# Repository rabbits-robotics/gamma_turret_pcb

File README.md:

# gamma_turret_pcb

## 役割

砲塔側の制御基板。M5Stack Stamp-P4（ESP32-P4）を載せ、CAN 2 系統、射出 ESC の PWM 2ch、装填サーボの半二重 UART、上位コントローラとの UART、IMU を 1 枚にまとめる。

## 主要部品

| 部品 | 型番 | 用途 |
|---|---|---|
| マイコンモジュール | M5Stack Stamp-P4（ESP32-P4） | 制御。ピンソケットで差し替え可 |
| CAN トランシーバ | MCP2562-E/P × 2 | CAN1（砲塔・ジンバル系）、CAN2（車体系） |
| レギュレータ | M78AR05-1 | 24V → 5V（Stamp-P4 用） |
| IMU | BNO055 | 姿勢。UART 接続 |
| 24V コネクタ | AMASS XT30PW-M × 2、XT30PW-F × 1 | 24V 入力、外部 DCDC への往復 |
| CAN / ESC 信号 | JST PH S2B-PH-K × 4 | CAN1、CAN2、射出 ESC 左右 |
| ESC 電源 | JST XH S2B-XH-A × 2 | 射出 ESC 左右 |
| サーボ / 上位 UART | JST XH S3B-XH-A × 2 | ST3215（半二重）、上位コントローラ |
| CAN 終端抵抗 | 120 Ω × 2 | CAN1 / CAN2 |
| 表示・操作 | LED × 6、タクト SW × 2 | 電源 / デバッグ / アクティビティ、BOOT / RESET |

回路図は [gamma_turret.pdf](./gamma_turret.pdf)、部品表は [bom.csv](./bom.csv)、3D は [gamma_turret.step](./gamma_turret.step)。
設計時の検討は [docs/](./docs/) に、旧 STM32 版の設計は [old_design/](./old_design/) に残している。

## v1.0 の注意

- 未配線 1 箇所をジャンパで対応している（D1 のアノード側。[docs/2026-10-18-v1.0-power-on.md](./docs/2026-10-18-v1.0-power-on.md)）
- Stamp-P4 の USB-C から基板の 5V 系へ電流が流れる。USB だけで 5V 系（CAN トランシーバ、LED、UART）は動く。24V と USB を同時につないでも実用上は問題ないが、設計意図ではないため改版で逆流防止を入れる予定

## ライセンス

© Rabbits Robotics、[CERN-OHL-P-2.0](./LICENSE)。

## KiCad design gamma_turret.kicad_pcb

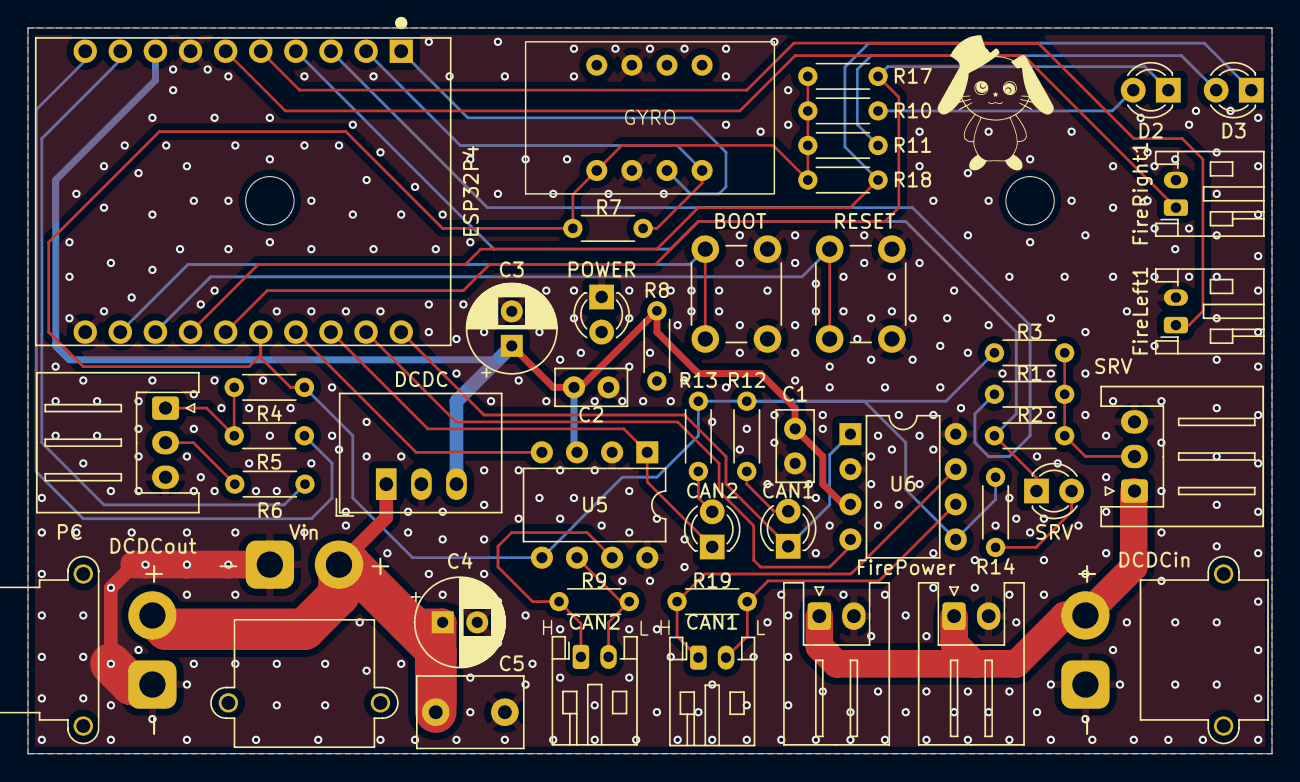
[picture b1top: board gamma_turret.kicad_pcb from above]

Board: 2 copper layers, 90.0 x 52.5 mm, 46 parts (0 on the bottom side), 34 nets.

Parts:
BOOT: SW_Push; SW_PUSH_6mm
C1, C2: 100n; C_Disc_D5.0mm_W2.5mm_P2.50mm
C3, C4: 100u; CP_Radial_D6.3mm_P2.50mm
C5: 22u; C_Disc_D7.5mm_W5.0mm_P5.00mm
CAN1, CAN2#2: LED; LED_D3.0mm
CAN1#2, CAN2: Conn_01x02; JST_PH_S2B-PH-K_1x02_P2.00mm_Horizontal
D2, D3: LED; LED_D3.0mm
DCDC: M78AR05-1; Converter_DCDC_RECOM_R-78E-0.5_THT
DCDCin: Conn_01x02; AMASS_XT30PW-M_1x02_P2.50mm_Horizontal
DCDCout: Conn_01x02; AMASS_XT30PW-F_1x02_P2.50mm_Horizontal
ESP32P4: M5Stack_Stamp-P4; Stamp-P4_Socket_2x10_P2.54mm_RS20.32mm
FireLeft1: Conn_01x02; JST_PH_S2B-PH-K_1x02_P2.00mm_Horizontal
FirePower, FirePower2: Conn_01x02; JST_XH_S2B-XH-A_1x02_P2.50mm_Horizontal
FireRight1: Conn_01x02; JST_PH_S2B-PH-K_1x02_P2.00mm_Horizontal
GYRO: BNO055
PC: Conn_01x03; JST_XH_S3B-XH-A_1x03_P2.50mm_Horizontal
POWER: LED; LED_D3.0mm
R1, R2, R8, R10, R11, R12, R13, R14: 1k; R_Axial_DIN0204_L3.6mm_D1.6mm_P5.08mm_Horizontal
R3, R4, R7, R17, R18: 10k; R_Axial_DIN0204_L3.6mm_D1.6mm_P5.08mm_Horizontal
R5, R6: 220; R_Axial_DIN0204_L3.6mm_D1.6mm_P5.08mm_Horizontal
R9, R19: 120; R_Axial_DIN0204_L3.6mm_D1.6mm_P5.08mm_Horizontal
RESET: SW_Push; SW_PUSH_6mm
SRV: LED; LED_D3.0mm
SRV#2: Conn_01x03; JST_XH_S3B-XH-A_1x03_P2.50mm_Horizontal
U5, U6: MCP2562-E-P; DIP-8_W7.62mm
Vin: Conn_01x02; AMASS_XT30PW-M_1x02_P2.50mm_Horizontal

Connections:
+3V3: ESP32P4.15 (3V3_OUT), GYRO.1 (VIN), R3.1, R4.1, R7.1, R10.1, R11.1, R12.1, R13.1, R14.1, R17.1, R18.1, U5.5 (Vio), U6.5 (Vio)
+5V: C1.1, C2.1, C3.1, DCDC.3 (VOUT), ESP32P4.8 (VBUS_5V), R8.1, U5.3 (VDD), U6.3 (VDD)
+7.5V: DCDCin.2, FirePower.1, FirePower2.1, SRV#2.1
+24V: C4.1, C5.1, DCDC.1 (VIN), DCDCout.2, Vin.2
/CAN1_RX: ESP32P4.12 (G21), U6.4 (RXD)
/CAN1_TX: CAN1.1 (K), ESP32P4.11 (G23), U6.1 (TXD)
/CAN2_RX: ESP32P4.14 (G17), U5.4 (RXD)
/CAN2_TX: CAN2#2.1 (K), ESP32P4.13 (G19), U5.1 (TXD)
/FIRE_LEFT_MOTOR: ESP32P4.5 (G1), FireLeft1.1
/FIRE_RIGHT_MOTOR: ESP32P4.6 (G0), FireRight1.1
/IMU_RX: ESP32P4.1 (G15), GYRO.3 (SDA/T)
/IMU_TX: ESP32P4.2 (G12), GYRO.4 (SCL/R), R7.2
/PC_RX: ESP32P4.9 (G27), R6.1
/PC_TX: ESP32P4.10 (G26), R5.1
/SRV_RX: ESP32P4.3 (G10), R1.1
/SRV_TX: ESP32P4.4 (G8), R2.2, SRV.1 (K)
GND: BOOT.2, C1.2, C2.2, C3.2, C4.2, C5.2, DCDC.2 (GND), DCDCin.1, DCDCout.1, ESP32P4.7 (GND), ESP32P4.20 (GND), FireLeft1.2, FirePower.2, FirePower2.2, FireRight1.2, GYRO.2 (GND), GYRO.7 (GND), PC.3, POWER.1 (K), RESET.2, SRV#2.3, U5.2 (VSS), U5.8 (STBY), U6.2 (VSS), U6.8 (STBY), Vin.1
unnamed: CAN1#2.1, R19.1, U6.7 (CANH)
unnamed: CAN1#2.2, R19.2, U6.6 (CANL)
unnamed: CAN2.1, R9.1, U5.7 (CANH)
unnamed: CAN2.2, R9.2, U5.6 (CANL)
unnamed: POWER.2 (A), R8.2
unnamed: D2.2 (A), R10.2
unnamed: D2.1 (K), ESP32P4.16 (G37), R17.2
unnamed: D3.2 (A), R11.2
unnamed: D3.1 (K), ESP32P4.17 (G38), R18.2
unnamed: CAN1.2 (A), R12.2
unnamed: CAN2#2.2 (A), R13.2
unnamed: R14.2, SRV.2 (A)
unnamed: PC.1, R4.2, R5.2
unnamed: PC.2, R6.2
unnamed: R1.2, R2.1, R3.2, SRV#2.2
unnamed: ESP32P4.18 (EN), RESET.1
unnamed: BOOT.1, ESP32P4.19 (G35_BOOT)

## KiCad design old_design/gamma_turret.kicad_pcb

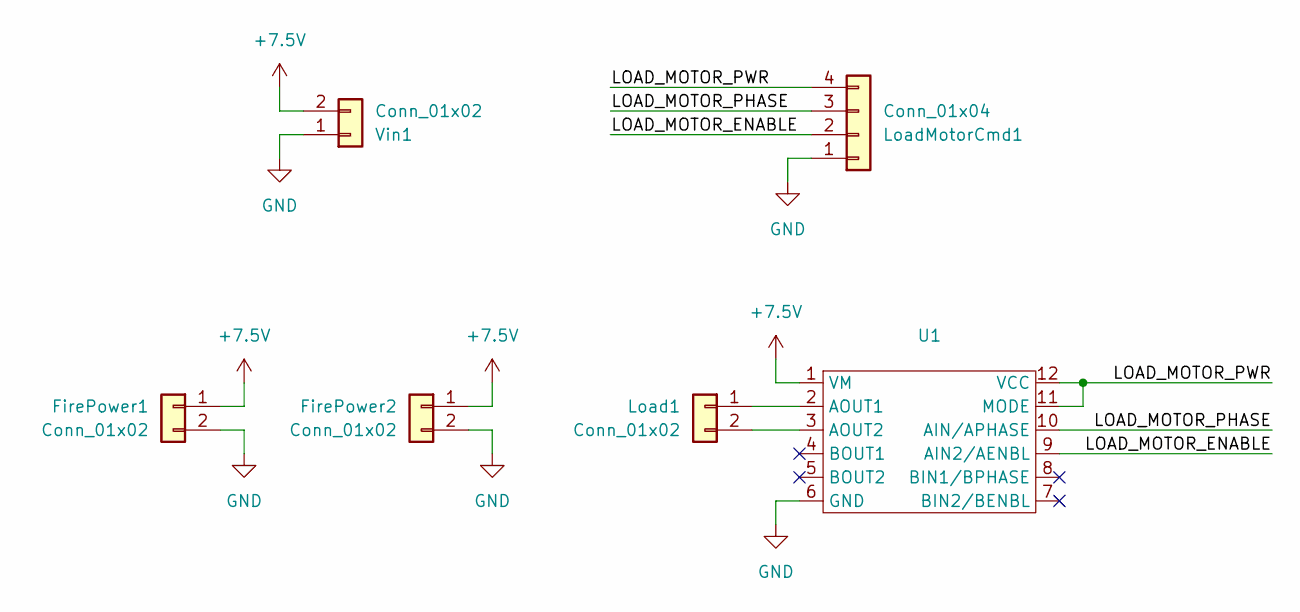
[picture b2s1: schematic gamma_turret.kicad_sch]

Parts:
FirePower1, FirePower2: Conn_01x02; JST_XH_B2B-XH-A_1x02_P2.50mm_Vertical
Load1: Conn_01x02; JST_PH_B2B-PH-K_1x02_P2.00mm_Vertical
LoadMotorCmd1: Conn_01x04; JST_PH_B4B-PH-K_1x04_P2.00mm_Vertical
U1: DRV8835
Vin1: Conn_01x02; TerminalBlock_bornier-2_P5.08mm

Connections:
+7.5V: FirePower1.1, FirePower2.1, U1.1 (VM), Vin1.2
/LOAD_MOTOR_ENABLE: LoadMotorCmd1.2, U1.9 (AIN2/AENBL)
/LOAD_MOTOR_PHASE: LoadMotorCmd1.3, U1.10 (AIN/APHASE)
/LOAD_MOTOR_PWR: LoadMotorCmd1.4, U1.11 (MODE), U1.12 (VCC)
GND: FirePower1.2, FirePower2.2, LoadMotorCmd1.1, U1.6 (GND), Vin1.1
unnamed: Load1.1, U1.2 (AOUT1)
unnamed: Load1.2, U1.3 (AOUT2)

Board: 2 copper layers, 6 parts (0 on the bottom side), 7 nets, no tracks yet.
